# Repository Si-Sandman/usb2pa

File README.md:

USB2PA Project <br>
USB2 Protocol Analyzer Wing for the Papilio-Pro FPGA Board.

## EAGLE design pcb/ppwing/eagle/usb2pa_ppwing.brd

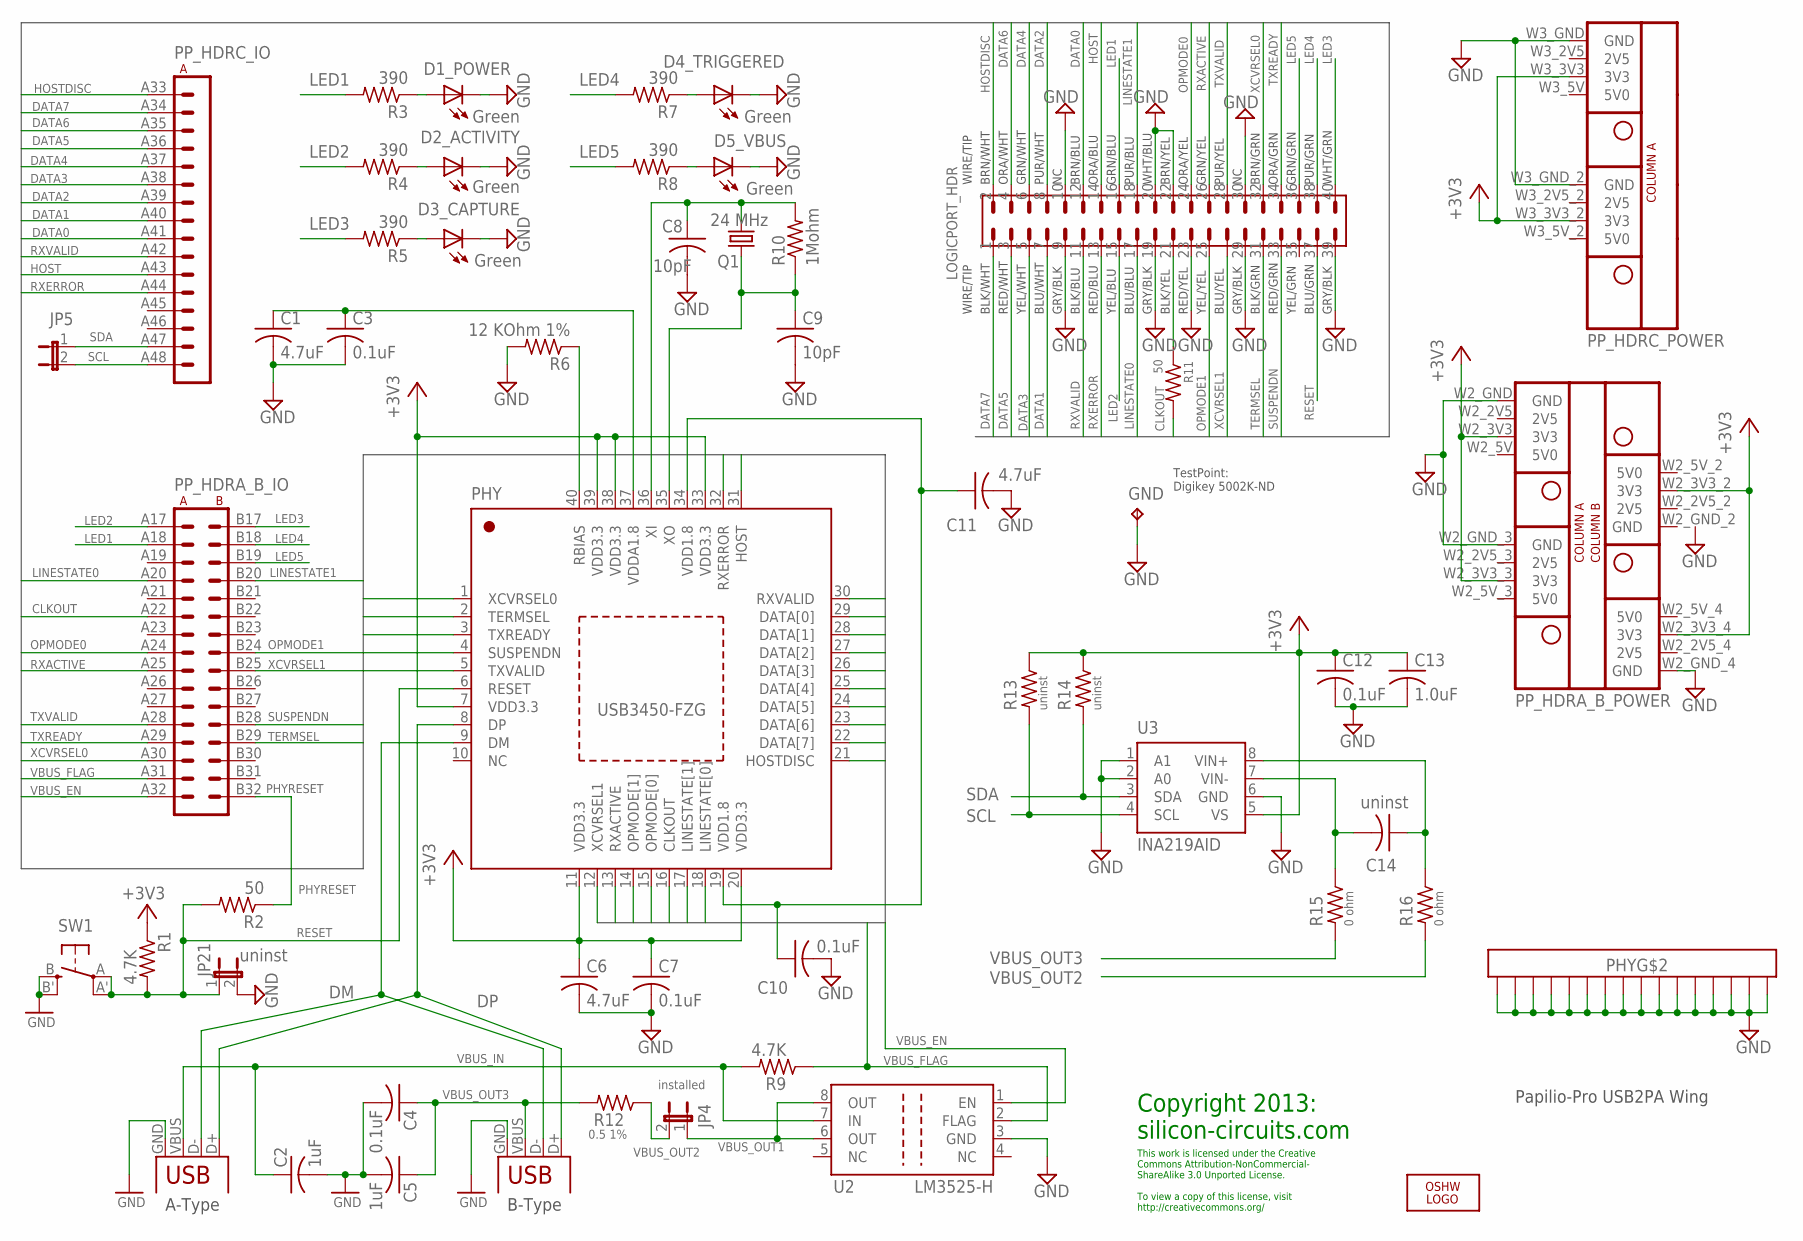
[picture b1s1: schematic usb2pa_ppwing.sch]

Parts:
C1, C6, C11: 4.7uF; C0805
C2, C5: 1uF; C0805
C3, C4, C7, C10, C12: 0.1uF; C0805
C8, C9: 10pF; C0805
C13: 1.0uF; C0805
C14: uninst; C0805
CC_LICENSE: CC_LICENSE
D1_POWER, D2_ACTIVITY, D3_CAPTURE, D4_TRIGGERED, D5_VBUS: Green; CHIPLED_0805
DEVICE: USB-B; USB-B-PTH
GND: TPPAD1-13; P1-13
HOST: USB-A-FEMALE-SPARKFUN_PRT-09011; USB_TYPE_A_FEMALE
JP4: installed; JP1
JP5, JP21: uninst; JP1
LOGICPORT_HDR: LOGICPORT_HDR_2X20; LOGICPORT_2X20_HEADER
LOGO1: OSHW_LOGO_FILLX0350-NT; OSHW_FILLX350_NOTEXT
PHY: USB3450-FZG; QFN40-6X6
PP_HDR: MEGAWING_FULL_P1MEGAWING_P1; MEGAWING_FULL_NOHOLES_P1
Q1: 24 MHz; HC49UP
R1, R9: 4.7K; R0805
R2, R11: 50; R0805
R3, R4, R5, R7, R8: 390; R0805
R6: 12 KOhm 1%; R0805
R10: 1Mohm; R0805
R12: 0.5 1%; R0805
R13, R14: uninst; R0805
R15, R16: 0 ohm; R0805
SW1: EVQQ2; EVQ-Q2
U2: LM3525-H; D_R-PDSO-G08
U3: INA219AID; D-R-PDSO-G8

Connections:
+3V3: C6.1, C7.1, C12.1, C13.1, PHY.7 (VDD3.3), PHY.11 (VDD3.3), PHY.20 (VDD3.3), PHY.33 (VDD3.3), PHY.38 (VDD3.3), PHY.39 (VDD3.3), PP_HDR.W2_3V3 (3V3), PP_HDR.W2_3V3_2 (3V3), PP_HDR.W2_3V3_3 (3V3), PP_HDR.W2_3V3_4 (3V3), PP_HDR.W3_3V3 (3V3), PP_HDR.W3_3V3_2 (3V3), R1.1, R13.1, R14.1, U3.5 (VS)
CLKOUT: PHY.16 (CLKOUT), PP_HDR.A22 (A6), R11.2
DATA0: LOGICPORT_HDR.12, PHY.29 (DATA[0]), PP_HDR.A41 (A9)
DATA1: LOGICPORT_HDR.7, PHY.28 (DATA[1]), PP_HDR.A40 (A8)
DATA2: LOGICPORT_HDR.8, PHY.27 (DATA[2]), PP_HDR.A39 (A7)
DATA3: LOGICPORT_HDR.5, PHY.26 (DATA[3]), PP_HDR.A38 (A6)
DATA4: LOGICPORT_HDR.6, PHY.25 (DATA[4]), PP_HDR.A37 (A5)
DATA5: LOGICPORT_HDR.3, PHY.24 (DATA[5]), PP_HDR.A36 (A4)
DATA6: LOGICPORT_HDR.4, PHY.23 (DATA[6]), PP_HDR.A35 (A3)
DATA7: LOGICPORT_HDR.1, PHY.22 (DATA[7]), PP_HDR.A34 (A2)
DM: DEVICE.D-, HOST.D-, PHY.9 (DM)
DP: DEVICE.D+, HOST.D+, PHY.8 (DP)
GND: C1.2, C2.2, C3.2, C4.2, C5.2, C6.2, C7.2, C8.2, C9.2, C10.2, C11.2, C12.2, C13.2, D1_POWER.C, D2_ACTIVITY.C, D3_CAPTURE.C, D4_TRIGGERED.C, D5_VBUS.C, DEVICE.GND, GND.TP, HOST.GND, JP21.2, LOGICPORT_HDR.9, LOGICPORT_HDR.10, LOGICPORT_HDR.19, LOGICPORT_HDR.20, LOGICPORT_HDR.22, LOGICPORT_HDR.23, LOGICPORT_HDR.29, LOGICPORT_HDR.30, LOGICPORT_HDR.39, PHY.GND@1 (EXP16), PHY.GND@2 (EXP16), PHY.GND@3 (EXP16), PHY.GND@4 (EXP16), PHY.GND@5 (EXP16), PHY.GND@6 (EXP16), PHY.GND@7 (EXP16), PHY.GND@8 (EXP16), PHY.GND@9 (EXP16), PHY.GND@10 (EXP16), PHY.GND@11 (EXP16), PHY.GND@12 (EXP16), PHY.GND@13 (EXP16), PHY.GND@14 (EXP16), PHY.GND@15 (EXP16), PHY.GND@16 (EXP16), PP_HDR.W2_GND (GND), PP_HDR.W2_GND_2 (GND), PP_HDR.W2_GND_3 (GND), PP_HDR.W2_GND_4 (GND), PP_HDR.W3_GND (GND), PP_HDR.W3_GND_2 (GND), R6.2, SW1.B (S), SW1.B' (S1), U2.3 (GND), U3.1 (A1), U3.2 (A0), U3.6 (GND)
HOST: LOGICPORT_HDR.14, PHY.31 (HOST), PP_HDR.A43 (A11)
HOSTDISC: LOGICPORT_HDR.2, PHY.21 (HOSTDISC), PP_HDR.A33 (A1)
LED1: LOGICPORT_HDR.16, PP_HDR.A18 (A2), R3.2
LED2: LOGICPORT_HDR.15, PP_HDR.A17 (A1), R4.2
LED3: LOGICPORT_HDR.40, PP_HDR.B17 (B1), R5.2
LED4: LOGICPORT_HDR.38, PP_HDR.B18 (B2), R7.2
LED5: LOGICPORT_HDR.36, PP_HDR.B19 (B3), R8.2
LINESTATE0: LOGICPORT_HDR.17, PHY.18 (LINESTATE[0]), PP_HDR.A20 (A4)
LINESTATE1: LOGICPORT_HDR.18, PHY.17 (LINESTATE[1]), PP_HDR.B20 (B4)
unnamed: LOGICPORT_HDR.21, R11.1
unnamed: D2_ACTIVITY.A, R4.1
unnamed: D3_CAPTURE.A, R5.1
unnamed: D5_VBUS.A, R8.1
unnamed: D4_TRIGGERED.A, R7.1
unnamed: D1_POWER.A, R3.1
OPMODE0: LOGICPORT_HDR.24, PHY.15 (OPMODE[0]), PP_HDR.A24 (A8)
OPMODE1: LOGICPORT_HDR.25, PHY.14 (OPMODE[1]), PP_HDR.B24 (B8)
PHYRESET: PP_HDR.B32 (B16), R2.1
RBIAS: PHY.40 (RBIAS), R6.1
RESET: JP21.1, LOGICPORT_HDR.37, PHY.6 (RESET), R1.2, R2.2, SW1.A, SW1.A' (P1)
RXACTIVE: LOGICPORT_HDR.26, PHY.13 (RXACTIVE), PP_HDR.A25 (A9)
RXERROR: LOGICPORT_HDR.13, PHY.32 (RXERROR), PP_HDR.A44 (A12)
RXVALID: LOGICPORT_HDR.11, PHY.30 (RXVALID), PP_HDR.A42 (A10)
SCL: JP5.2, PP_HDR.A48 (A16), R13.2, U3.4 (SCL)
SDA: JP5.1, PP_HDR.A47 (A15), R14.2, U3.3 (SDA)
SUSPENDN: LOGICPORT_HDR.33, PHY.4 (SUSPENDN), PP_HDR.B28 (B12)
TERMSEL: LOGICPORT_HDR.31, PHY.2 (TERMSEL), PP_HDR.B29 (B13)
TXREADY: LOGICPORT_HDR.34, PHY.3 (TXREADY), PP_HDR.A29 (A13)
TXVALID: LOGICPORT_HDR.28, PHY.5 (TXVALID), PP_HDR.A28 (A12)
VBUS_EN: PP_HDR.A32 (A16), U2.1 (EN)
VBUS_FLAG: PP_HDR.A31 (A15), R9.1, U2.2 (FLAG)
VBUS_IN: C2.1, HOST.VBUS, R9.2, U2.7 (IN)
VBUS_OUT1: JP4.1, U2.6 (OUT), U2.8 (OUT)
VBUS_OUT2: JP4.2, R12.1, R16.2
VBUS_OUT3: C4.1, C5.1, DEVICE.VBUS, R12.2, R15.2
VDD1.8: C10.1, C11.1, PHY.19 (VDD1.8), PHY.34 (VDD1.8)
VDDA1.8: C1.1, C3.1, PHY.37 (VDDA1.8)
VIN+: C14.1, R16.1, U3.8 (VIN+)
VIN-: C14.2, R15.1, U3.7 (VIN-)
XCVRSEL0: LOGICPORT_HDR.32, PHY.1 (XCVRSEL0), PP_HDR.A30 (A14)
XCVRSEL1: LOGICPORT_HDR.27, PHY.12 (XCVRSEL1), PP_HDR.B25 (B9)
XI: C8.1, PHY.36 (XI), Q1.2, R10.2
XO: C9.1, PHY.35 (XO), Q1.1, R10.1

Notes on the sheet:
Papilio-Pro USB2PA Wing
B-Type
A-Type
TestPoint: Digikey 5002K-ND
Copyright 2013: silicon-circuits.com
This work is licensed under the Creative Commons Attribution-NonCommercial- ShareAlike 3.0 Unported License. To view a copy of this license, visit http://creativecommons.org/

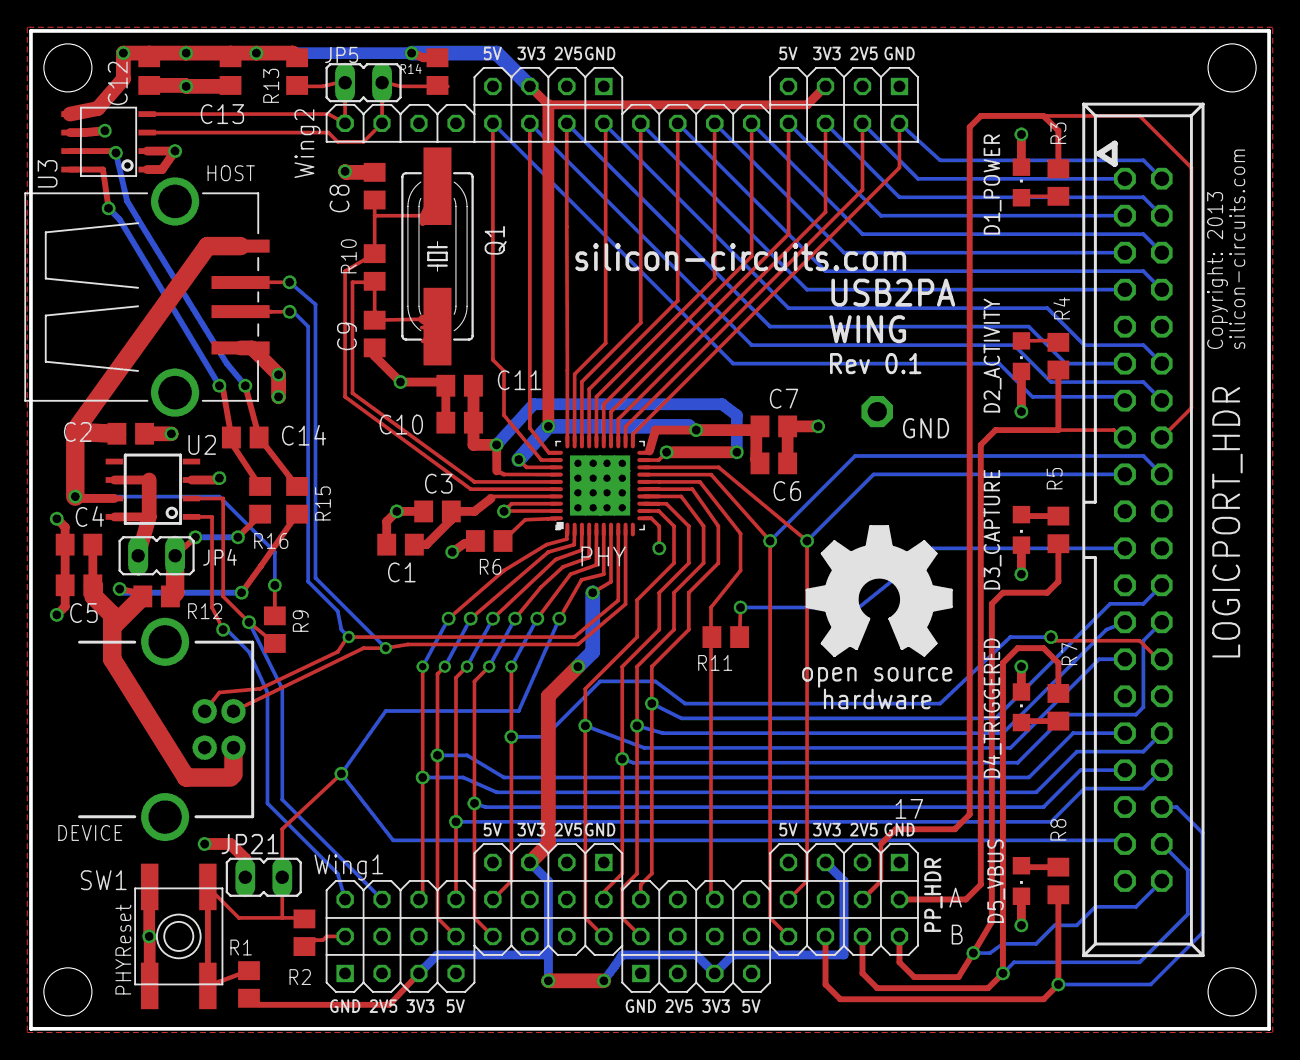
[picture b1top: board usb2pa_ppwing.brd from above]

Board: 2 copper layers, 85.1 x 68.6 mm, 54 parts (0 on the bottom side), 56 nets.

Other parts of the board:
JP1, JP2, JP3, JP7: STAND-OFF

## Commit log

2013-09-22 Initial commit for usb2pa rev0p1 prototyping board.
2013-09-22 REV0P1a : This is what was actually submitted to the board shop.
2013-09-22 Adding README for github.
2013-09-22 Fixed README filename extension
2013-09-22 Adding LICENSE file.

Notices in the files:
parts and their libraries:
SparkFun-Connectors: Licensing: CC v3.0 Share-Alike You are welcome to use this library for commercial purposes.
